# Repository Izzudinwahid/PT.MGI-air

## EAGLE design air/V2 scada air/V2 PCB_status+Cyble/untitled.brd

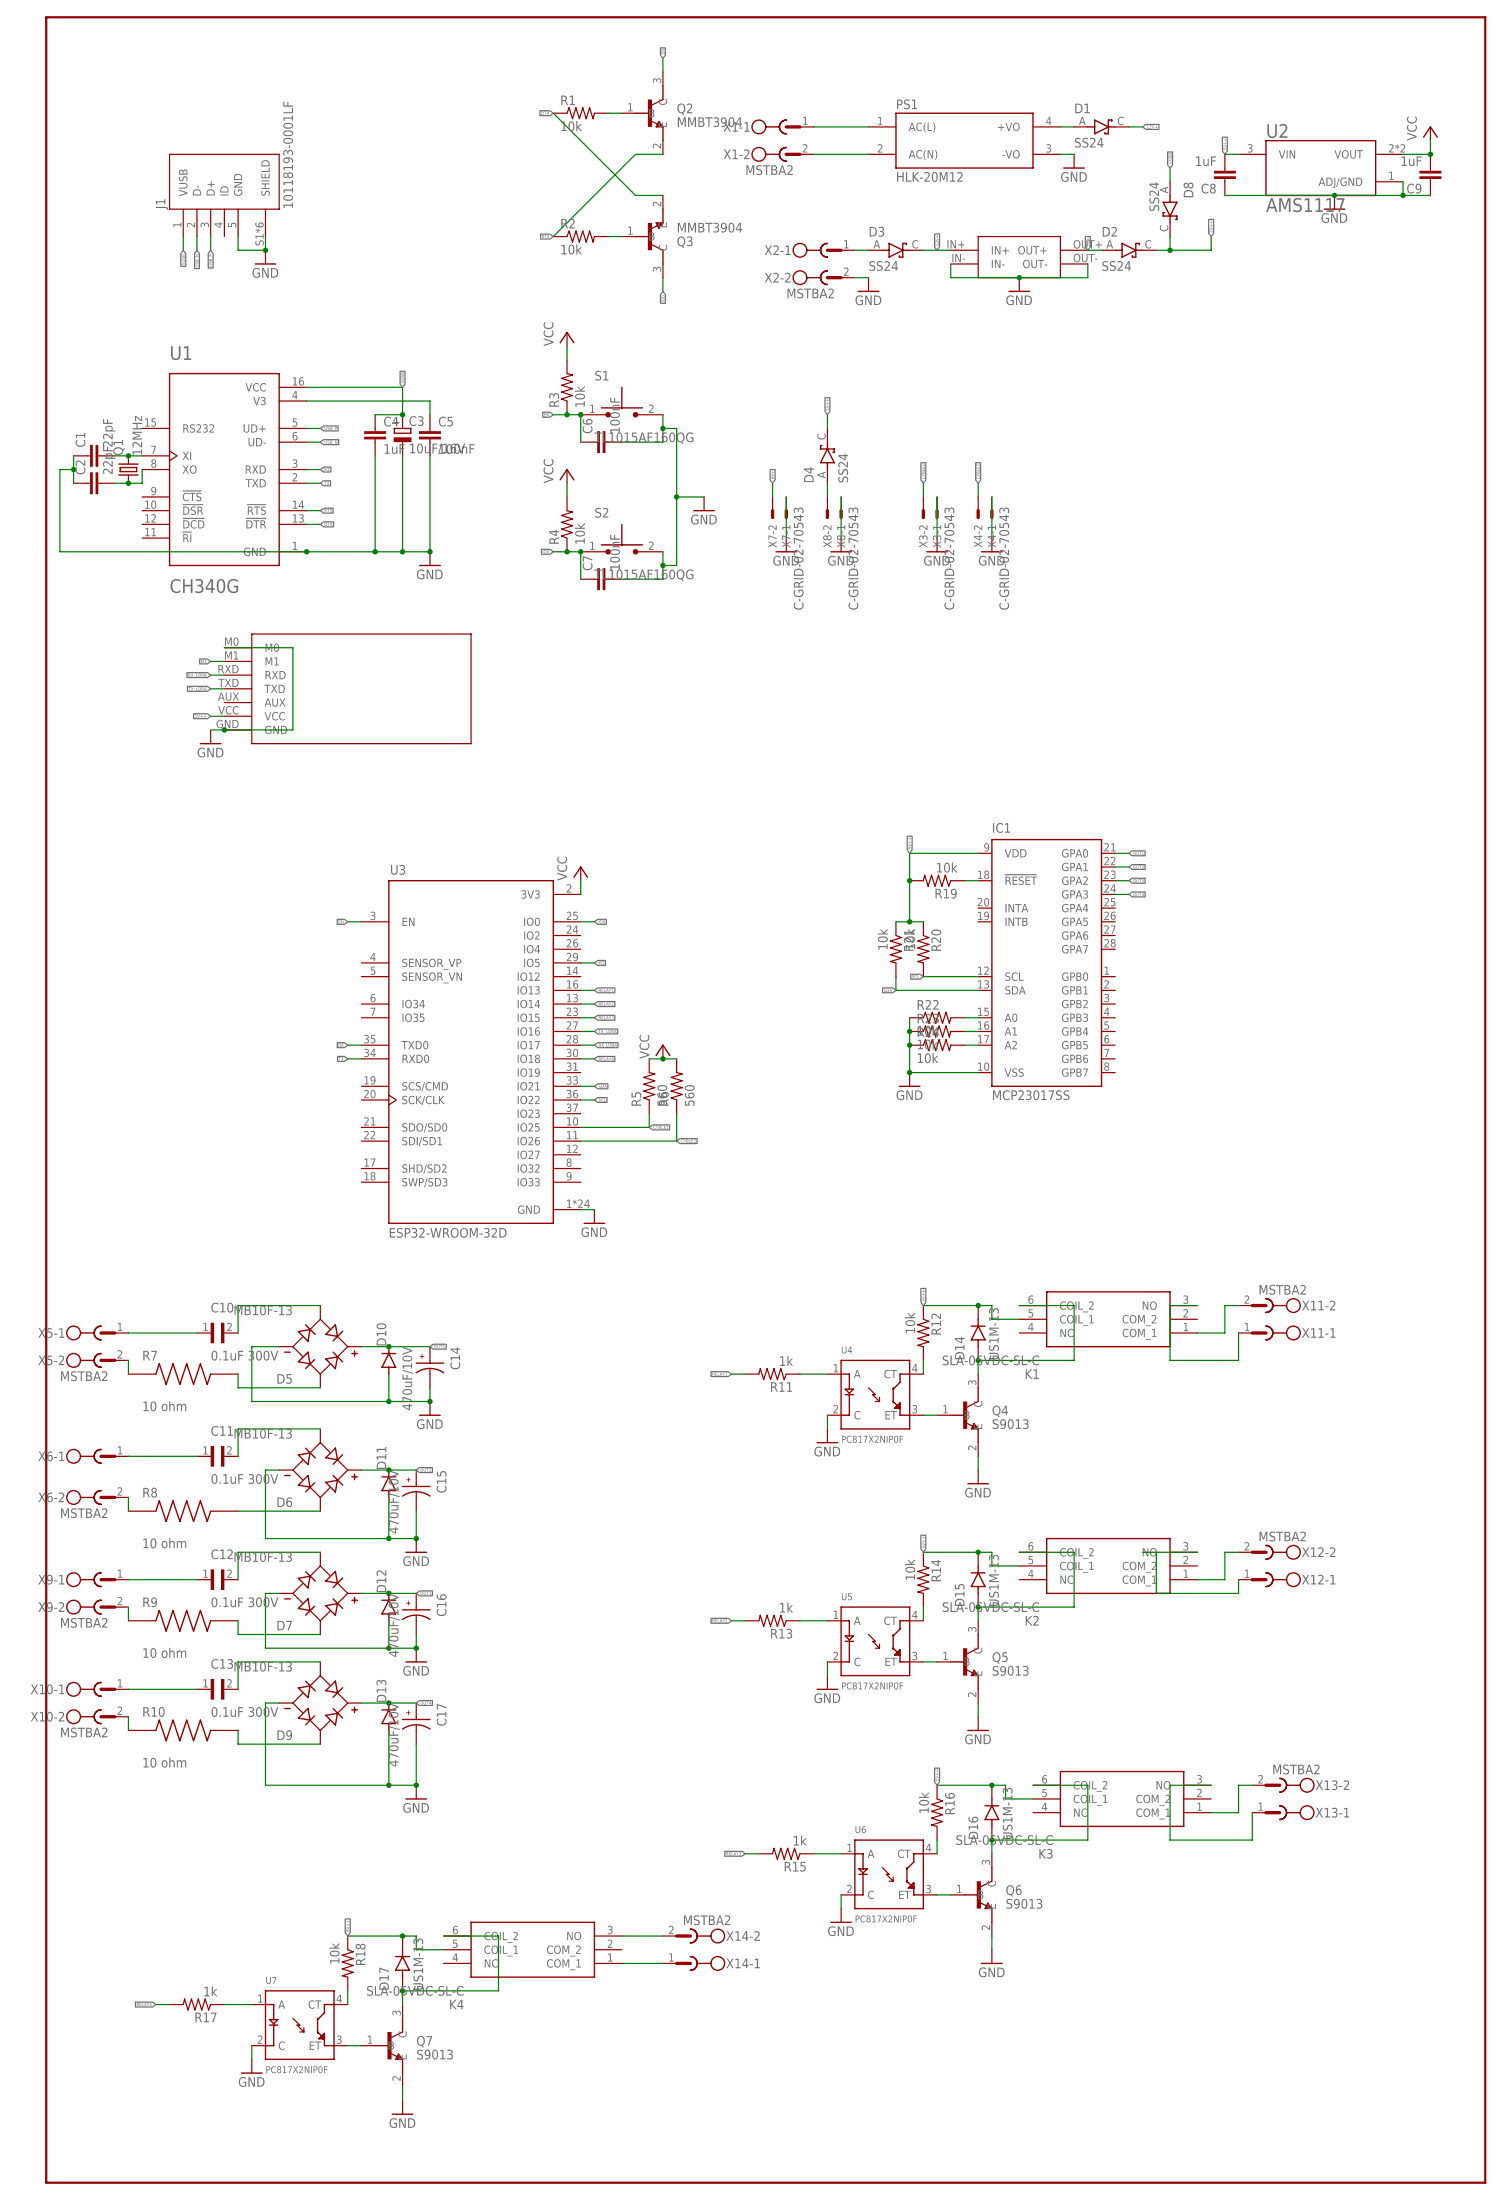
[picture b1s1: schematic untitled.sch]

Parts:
C1, C2: 22pF; C0805K
C3: 10uF/16V; 153CLV-0505
C4, C8, C9: 1uF; C0805K
C5, C6, C7: 100nF; C0805K
C10, C11, C12, C13: 0.1uF 300V; CAPRR1500W60L1750T500H1200
C14, C15, C16, C17: 470uF/10V; CAP_EEEFC1A471AP
D1, D2, D3, D4, D8: SS24; DIOM5336X265N
D5, D6, D7, D9: MB10F-13; DIOB_MB10F-13
D10, D11, D12, D13: DIODE-SOD123; SOD123
D14, D15, D16, D17: US1M-13; DIOM5226X240N
EBYTEE220-900T22D1: EBYTEE220-900T22D
IC1: MCP23017SS; SSOP28
J1: 10118193-0001LF; FCI_10118193-0001LF
K1, K2, K3, K4: SLA-05VDC-SL-C; SLA05VDCSLC
MINI1: MINI560
PS1: HLK-20M12; CONV_HLK-20M12
Q1: 12MHz; SM49
Q2, Q3: MMBT3904; SOT95P240X120-3N
Q4, Q5, Q6, Q7: S9013; SOT95P240X120-3N
R1, R2, R3, R4, R12, R14, R16, R18, R19, R20, R21, R22, R23, R24: 10k; M0805
R5, R6: 560; M0805
R7, R8, R9, R10: 10 ohm; RES_ERJP14J200U
R11, R13, R15, R17: 1k; M0805
S1, S2: TL1015AF160QG; SW_TL1015AF160QG
U1: CH340G; SOIC127P600X180-16N
U2: AMS1117; SOT229P700X180-4N
U3: ESP32-WROOM-32D; MODULE_ESP32-WROOM-32D
U4, U5, U6, U7: PC817X2NIP0F; SOT254P975X400-4N
X1, X2, X5, X6, X9, X10, X11, X12, X13, X14: MSTBA2
X3, X4, X7, X8: C-GRID-02-70543; 70543-02

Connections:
5V+: D2.A, MINI1.OUT+, X7.2
5V++: C8.2, D2.C (K), D4.C (K), D8.C (K), D14.C (K), D15.C (K), D16.C (K), D17.C (K), EBYTEE220-900T22D1.VCC, IC1.9 (VDD), K1.5 (COIL_1), K2.5 (COIL_1), K3.5 (COIL_1), K4.5 (COIL_1), R12.1, R14.1, R16.1, R18.1, R19.2, R20.1, R21.1, U2.3 (VIN)
12V+: D1.C (K), D3.C (K), MINI1.IN+
CYBLE1: R5.1, U3.10 (IO25), X3.2
CYBLE2: R6.1, U3.11 (IO26), X4.2
DTR: Q3.2 (E), R1.1, U1.13 (!DTR)
EN: C6.1, Q2.3 (C), R3.1, S1.1, U3.3 (EN)
GND: C1.1, C2.1, C3.-, C4.2, C5.2, C6.2, C7.2, C8.1, C9.1, C14.2, C15.2, C16.2, C17.2, D5.3 (-), D6.3 (-), D7.3 (-), D9.3 (-), D10.A, D11.A, D12.A, D13.A, EBYTEE220-900T22D1.GND, EBYTEE220-900T22D1.M0, IC1.10 (VSS), J1.5 (GND), J1.S1 (SHIELD), J1.S2 (SHIELD), J1.S3 (SHIELD), J1.S4 (SHIELD), J1.S5 (SHIELD), J1.S6 (SHIELD), MINI1.IN-, MINI1.OUT-, PS1.3 (-VO), Q4.2 (E), Q5.2 (E), Q6.2 (E), Q7.2 (E), R22.1, R23.1, R24.1, S1.2, S2.2, U1.1 (GND), U2.1 (ADJ/GND), U3.1 (GND), U3.15 (GND), U3.38 (GND), U3.39_1 (GND), U3.39_2 (GND), U3.39_3 (GND), U3.39_4 (GND), U3.39_5 (GND), U3.39_6 (GND), U3.39_7 (GND), U3.39_8 (GND), U3.39_9 (GND), U3.39_10 (GND), U3.39_11 (GND), U3.39_12 (GND), U3.39_13 (GND), U3.39_14 (GND), U3.39_15 (GND), U3.39_16 (GND), U3.39_17 (GND), U3.39_18 (GND), U3.39_19 (GND), U3.39_20 (GND), U3.39_21 (GND), U4.2 (C), U5.2 (C), U6.2 (C), U7.2 (C), X2.2, X3.1, X4.1, X7.1, X8.1
IO0: C7.1, Q3.3 (C), R4.1, S2.1, U3.25 (IO0)
M1: EBYTEE220-900T22D1.M1, U3.29 (IO5)
unnamed: PS1.1 (AC(L)), X1.1
unnamed: C5.1, U1.4 (V3)
unnamed: Q2.1 (B), R1.2
unnamed: C1.2, Q1.2, U1.7 (XI)
unnamed: C2.2, Q1.1, U1.8 (XO)
unnamed: Q3.1 (B), R2.2
unnamed: PS1.2 (AC(N)), X1.2
unnamed: C10.1, X5.1
unnamed: D1.A, PS1.4 (+VO)
unnamed: D3.A, X2.1
unnamed: C11.1, X6.1
unnamed: D4.A, X8.2
unnamed: C12.1, X9.1
unnamed: C13.1, X10.1
unnamed: C10.2, D5.4 (AC2)
unnamed: C11.2, D6.4 (AC2)
unnamed: C12.2, D7.4 (AC2)
unnamed: C13.2, D9.4 (AC2)
unnamed: R11.1, U4.1 (A)
unnamed: Q4.1 (B), U4.3 (ET)
unnamed: R12.2, U4.4 (CT)
unnamed: K1.1 (COM_1), X11.2
unnamed: K1.3 (NO), X11.1
unnamed: D14.A, K1.6 (COIL_2), Q4.3 (C)
unnamed: IC1.18 (!RESET), R19.1
unnamed: R13.1, U5.1 (A)
unnamed: R10.1, X10.2
unnamed: R9.1, X9.2
unnamed: R8.1, X6.2
unnamed: R7.1, X5.2
unnamed: D9.2 (AC1), R10.2
unnamed: D7.2 (AC1), R9.2
unnamed: D6.2 (AC1), R8.2
unnamed: D5.2 (AC1), R7.2
unnamed: Q5.1 (B), U5.3 (ET)
unnamed: R14.2, U5.4 (CT)
unnamed: D15.A, K2.6 (COIL_2), Q5.3 (C)
unnamed: K2.1 (COM_1), X12.2
unnamed: K2.3 (NO), X12.1
unnamed: IC1.15 (A0), R22.2
unnamed: R15.1, U6.1 (A)
unnamed: Q6.1 (B), U6.3 (ET)
unnamed: R16.2, U6.4 (CT)
unnamed: D16.A, K3.6 (COIL_2), Q6.3 (C)
unnamed: K3.1 (COM_1), X13.2
unnamed: K3.3 (NO), X13.1
unnamed: IC1.16 (A1), R23.2
unnamed: R17.1, U7.1 (A)
unnamed: Q7.1 (B), U7.3 (ET)
unnamed: R18.2, U7.4 (CT)
unnamed: D17.A, K4.6 (COIL_2), Q7.3 (C)
unnamed: K4.3 (NO), X14.2
unnamed: K4.1 (COM_1), X14.1
unnamed: IC1.17 (A2), R24.2
OUT1: C14.1, D5.1 (+), D10.C, IC1.21 (GPA0)
OUT2: C15.1, D6.1 (+), D11.C, IC1.22 (GPA1)
OUT3: C16.1, D7.1 (+), D12.C, IC1.23 (GPA2)
OUT4: C17.1, D9.1 (+), D13.C, IC1.24 (GPA3)
RELAY1: R11.2, U3.16 (IO13)
RELAY2: R13.2, U3.13 (IO14)
RELAY3: R15.2, U3.23 (IO15)
RELAY4: R17.2, U3.30 (IO18)
RTS: Q2.2 (E), R2.1, U1.14 (!RTS)
RX: U1.3 (RXD), U3.35 (TXD0)
RX_LORA: EBYTEE220-900T22D1.RXD, U3.28 (IO17)
SCL: IC1.12 (SCL), R20.2, U3.36 (IO22)
SDA: IC1.13 (SDA), R21.2, U3.33 (IO21)
TX: U1.2 (TXD), U3.34 (RXD0)
TX_LORA: EBYTEE220-900T22D1.TXD, U3.27 (IO16)
USB_N: J1.2 (D-), U1.6 (UD-)
USB_P: J1.3 (D+), U1.5 (UD+)
VCC: C9.2, R3.2, R4.2, R5.2, R6.2, U2.2 (VOUT), U2.4 (VOUT), U3.2 (3V3)
VUSB: C3.+, C4.1, D8.A, J1.1 (VUSB), U1.16 (VCC)

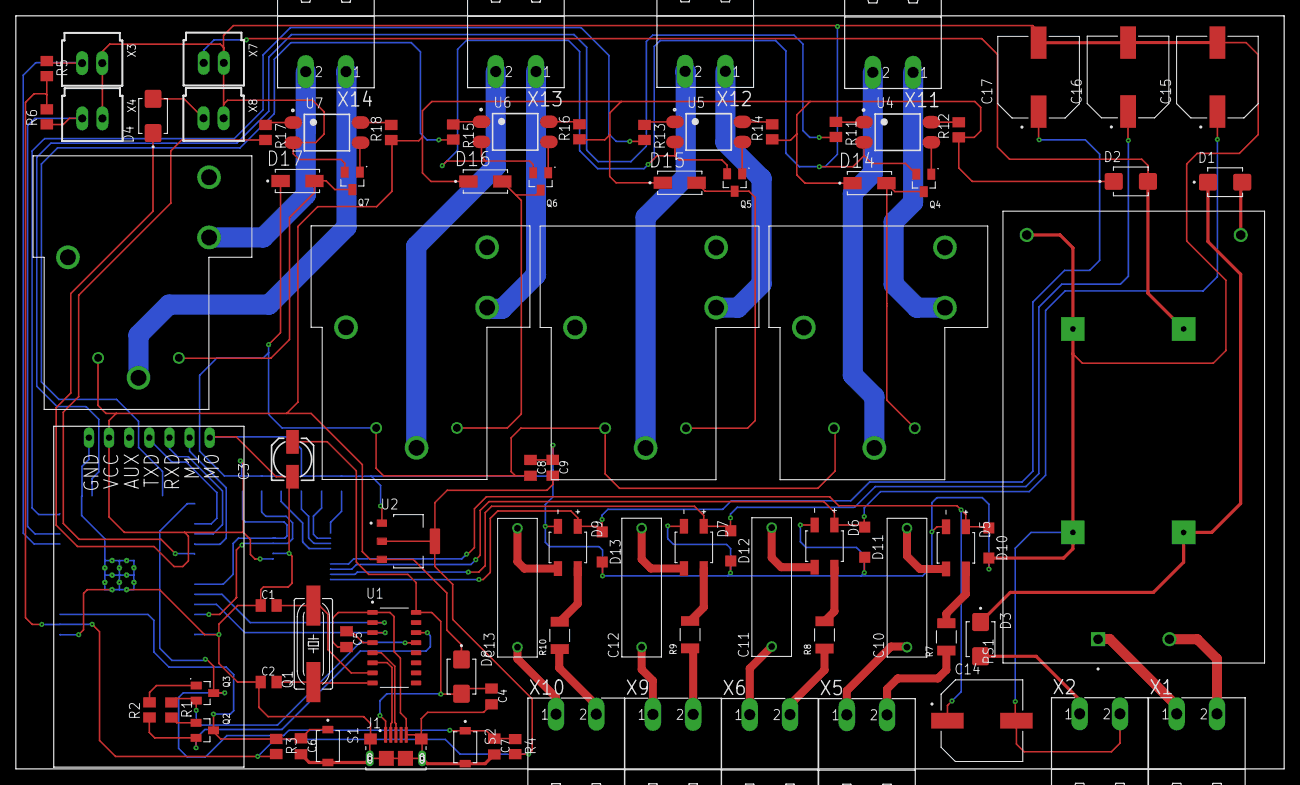
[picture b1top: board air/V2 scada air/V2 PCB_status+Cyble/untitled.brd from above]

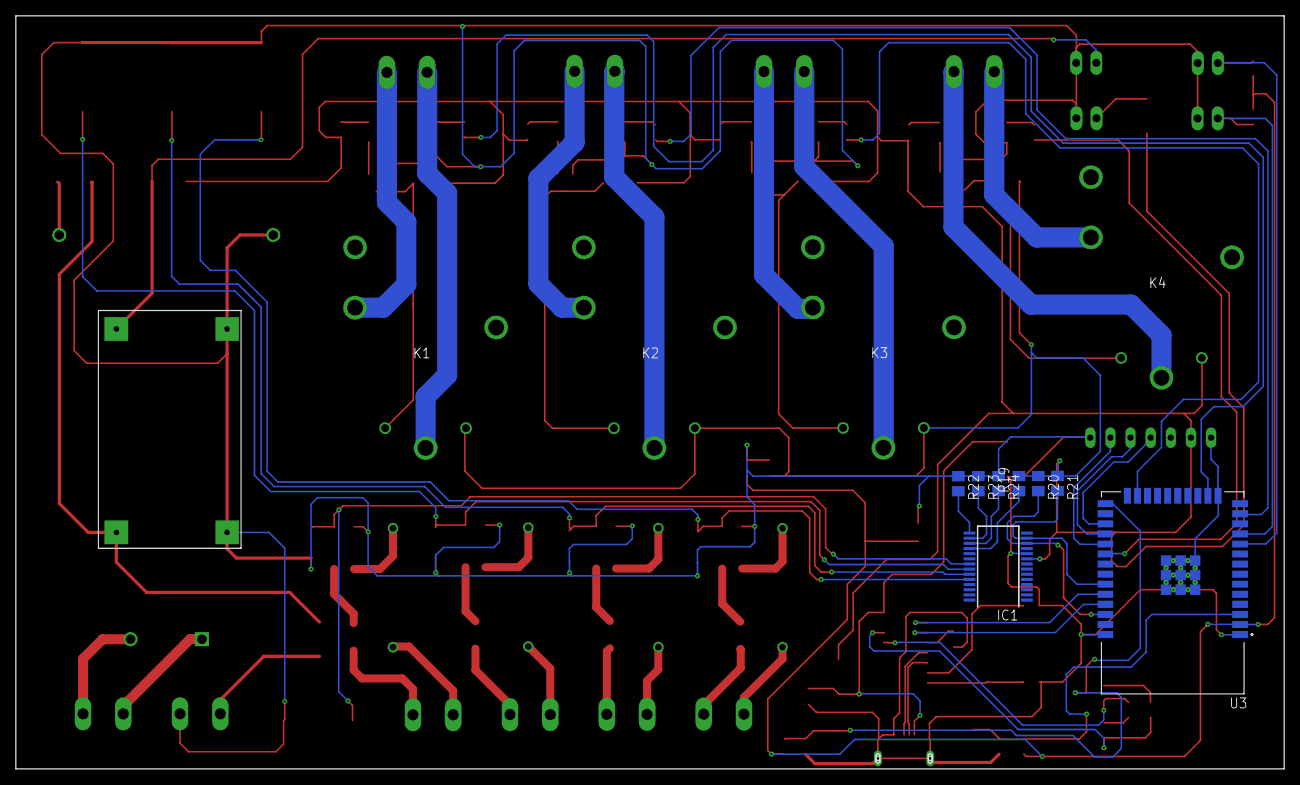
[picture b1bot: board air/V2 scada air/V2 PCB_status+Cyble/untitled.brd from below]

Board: 2 copper layers, 160.0 x 95.0 mm, 97 parts (13 on the bottom side), 83 nets.

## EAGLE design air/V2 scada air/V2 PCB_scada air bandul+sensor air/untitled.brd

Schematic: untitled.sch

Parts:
C1, C2: 22pF; C0805K
C3: 10uF/16V; 153CLV-0505
C4, C8, C9: 1uF; C0805K
C5, C6, C7: 100nF; C0805K
D1, D2, D3, D4, D8: SS24; DIOM5336X265N
D5, D7: US1M-13; DIOM5226X240N
EBYTEE220-900T22D1: EBYTEE220-900T22D
IC1, IC2: MCP23017SS; SSOP28
J1: 10118193-0001LF; FCI_10118193-0001LF
MINI1: MINI560
PS1: HLK-20M12; CONV_HLK-20M12
Q1: 12MHz; SM49
Q2, Q3: MMBT3904; SOT95P240X120-3N
Q5, Q6, Q7, Q8, Q9, Q10, Q11, Q12, Q13, Q14, Q15, Q16, Q17, Q18, Q19, Q20, Q21, Q22, Q23, Q24, Q25, Q26, Q27, Q28: MMBT2222; SOT23-BEC
R1, R2, R3, R4, R7, R8, R59, R60, R61, R62, R63, R64, R65, R66, R67, R68, R69, R70: 10k; M0805
R5, R6: 680; M0805
R11, R13, R15, R17, R19, R21, R23, R25, R27, R29, R31, R33, R35, R37, R39, R41, R43, R45, R47, R49, R51, R53, R55, R57: 1k; M0805
R12, R14, R16, R18, R20, R22, R24, R26, R28, R30, R32, R34, R36, R38, R40, R42, R44, R46, R48, R50, R52, R54, R56, R58: 30k; M0805
S1, S2: TL1015AF160QG; SW_TL1015AF160QG
TTL-RS1: TTL-RS485
U1: CH340G; SOIC127P600X180-16N
U2: AMS1117; SOT229P700X180-4N
U3: ESP32-WROOM-32D; MODULE_ESP32-WROOM-32D
X1, X2, X3: MSTBA2
X4: MSTBA4
X5: C-GRID-04-70543; 70543-04
X7, X8: C-GRID-02-70543; 70543-02
X10, X11, X12, X13, X14, X15, X16, X17, X18, X19, X20, X21, X22, X23, X24, X25, X26, X27, X28, X29, X30, X31, X32, X33: C-GRID-03-70543; 70543-03

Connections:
5V+: D2.A, MINI1.OUT+
5V++: C8.2, D2.C (K), D8.C (K), EBYTEE220-900T22D1.VCC, IC1.9 (VDD), IC2.9 (VDD), R5.2, R6.2, R11.1, R13.1, R15.1, R17.1, R19.1, R21.1, R23.1, R25.1, R27.1, R29.1, R31.1, R33.1, R35.1, R37.1, R39.1, R41.1, R43.1, R45.1, R47.1, R49.1, R51.1, R53.1, R55.1, R57.1, R59.2, R60.2, R61.1, R65.2, R66.2, R67.1, R68.2, TTL-RS1.VCC, U2.3 (VIN), X4.1, X5.4
12V: D1.A, PS1.4 (+VO), X7.2
12V+: D1.C (K), D3.C (K), D4.C (K), MINI1.IN+, R12.1, R14.1, R16.1, R18.1, R20.1, R22.1, R24.1, R26.1, R28.1, R30.1, R32.1, R34.1, R36.1, R38.1, R40.1, R42.1, R44.1, R46.1, R48.1, R50.1, R52.1, R54.1, R56.1, R58.1, X3.1, X10.3, X11.3, X12.3, X13.3, X14.3, X15.3, X16.3, X17.3, X18.3, X19.3, X20.3, X21.3, X22.3, X23.3, X24.3, X25.3, X26.3, X27.3, X28.3, X29.3, X30.3, X31.3, X32.3, X33.3
A+: TTL-RS1.A, X4.2
B-: TTL-RS1.B, X4.3
DTR: Q3.2 (E), R1.1, U1.13 (!DTR)
EN: C6.1, Q2.3 (C), R3.1, S1.1, U3.3 (EN)
GND: C1.1, C2.1, C3.-, C4.2, C5.2, C6.2, C7.2, C8.1, C9.1, EBYTEE220-900T22D1.GND, EBYTEE220-900T22D1.M0, IC1.10 (VSS), IC2.10 (VSS), J1.5 (GND), J1.S1 (SHIELD), J1.S2 (SHIELD), J1.S3 (SHIELD), J1.S4 (SHIELD), J1.S5 (SHIELD), J1.S6 (SHIELD), MINI1.IN-, MINI1.OUT-, PS1.3 (-VO), R62.2, R63.2, R64.2, R69.2, R70.2, S1.2, S2.2, TTL-RS1.GND, U1.1 (GND), U2.1 (ADJ/GND), U3.1 (GND), U3.15 (GND), U3.38 (GND), U3.39_1 (GND), U3.39_2 (GND), U3.39_3 (GND), U3.39_4 (GND), U3.39_5 (GND), U3.39_6 (GND), U3.39_7 (GND), U3.39_8 (GND), U3.39_9 (GND), U3.39_10 (GND), U3.39_11 (GND), U3.39_12 (GND), U3.39_13 (GND), U3.39_14 (GND), U3.39_15 (GND), U3.39_16 (GND), U3.39_17 (GND), U3.39_18 (GND), U3.39_19 (GND), U3.39_20 (GND), U3.39_21 (GND), X2.2, X3.2, X4.4, X5.1, X7.1, X8.1, X10.1, X11.1, X12.1, X13.1, X14.1, X15.1, X16.1, X17.1, X18.1, X19.1, X20.1, X21.1, X22.1, X23.1, X24.1, X25.1, X26.1, X27.1, X28.1, X29.1, X30.1, X31.1, X32.1, X33.1
IO0: C7.1, Q3.3 (C), R4.1, S2.1, U3.25 (IO0)
M1: EBYTEE220-900T22D1.M1, U3.29 (IO5)
unnamed: D5.C (K), U3.28 (IO17)
unnamed: C5.1, U1.4 (V3)
unnamed: Q2.1 (B), R1.2
unnamed: C1.2, Q1.2, U1.7 (XI)
unnamed: C2.2, Q1.1, U1.8 (XO)
unnamed: Q3.1 (B), R2.2
unnamed: PS1.1 (AC(L)), X1.1
unnamed: PS1.2 (AC(N)), X1.2
unnamed: D3.A, X2.1
unnamed: D4.A, X8.2
unnamed: Q5.B, R12.2
unnamed: IC2.18 (!RESET), R65.1
unnamed: Q5.E, X10.2
unnamed: D7.C (K), EBYTEE220-900T22D1.TXD
unnamed: Q6.B, R14.2
unnamed: IC1.18 (!RESET), R59.1
unnamed: Q6.E, X11.2
unnamed: Q7.B, R16.2
unnamed: IC1.15 (A0), R62.1
unnamed: Q7.E, X12.2
unnamed: Q8.B, R18.2
unnamed: IC1.16 (A1), R63.1
unnamed: Q8.E, X13.2
unnamed: Q9.B, R20.2
unnamed: IC1.17 (A2), R64.1
unnamed: Q9.E, X14.2
unnamed: Q10.B, R22.2
unnamed: IC2.15 (A0), R68.1
unnamed: Q10.E, X15.2
unnamed: Q11.B, R24.2
unnamed: IC2.16 (A1), R69.1
unnamed: Q11.E, X16.2
unnamed: Q12.B, R26.2
unnamed: IC2.17 (A2), R70.1
unnamed: Q12.E, X17.2
unnamed: Q13.B, R28.2
unnamed: Q13.E, X18.2
unnamed: Q14.B, R30.2
unnamed: Q14.E, X19.2
unnamed: Q15.B, R32.2
unnamed: Q15.E, X20.2
unnamed: Q16.B, R34.2
unnamed: Q16.E, X21.2
unnamed: Q17.B, R36.2
unnamed: Q17.E, X22.2
unnamed: Q18.B, R38.2
unnamed: Q18.E, X23.2
unnamed: Q19.B, R40.2
unnamed: Q19.E, X24.2
unnamed: Q20.B, R42.2
unnamed: Q20.E, X25.2
unnamed: Q21.B, R44.2
unnamed: Q21.E, X26.2
unnamed: Q22.B, R46.2
unnamed: Q22.E, X27.2
unnamed: Q23.B, R48.2
unnamed: Q23.E, X28.2
unnamed: Q24.B, R50.2
unnamed: Q24.E, X29.2
unnamed: Q25.B, R52.2
unnamed: Q25.E, X30.2
unnamed: Q26.B, R54.2
unnamed: Q26.E, X31.2
unnamed: Q27.B, R56.2
unnamed: Q27.E, X32.2
unnamed: Q28.B, R58.2
unnamed: Q28.E, X33.2
O1: IC1.21 (GPA0), Q5.C, R11.2
O2: IC1.22 (GPA1), Q6.C, R13.2
O3: IC1.23 (GPA2), Q7.C, R15.2
O4: IC1.24 (GPA3), Q8.C, R17.2
O5: IC1.25 (GPA4), Q9.C, R19.2
O6: IC1.26 (GPA5), Q10.C, R21.2
O7: IC1.27 (GPA6), Q11.C, R23.2
O8: IC1.28 (GPA7), Q12.C, R25.2
O9: IC1.1 (GPB0), Q13.C, R27.2
O10: IC1.2 (GPB1), Q14.C, R29.2
O11: IC1.3 (GPB2), Q15.C, R31.2
O12: IC1.4 (GPB3), Q16.C, R33.2
O13: IC1.5 (GPB4), Q17.C, R35.2
O14: IC1.6 (GPB5), Q18.C, R37.2
O15: IC1.7 (GPB6), Q19.C, R39.2
O16: IC1.8 (GPB7), Q20.C, R41.2
O17: IC2.21 (GPA0), Q21.C, R43.2
O18: IC2.22 (GPA1), Q22.C, R45.2
O19: IC2.23 (GPA2), Q23.C, R47.2
O20: IC2.24 (GPA3), Q24.C, R49.2
O21: IC2.25 (GPA4), Q25.C, R51.2
O22: IC2.26 (GPA5), Q26.C, R53.2
O23: IC2.27 (GPA6), Q27.C, R55.2
O24: IC2.28 (GPA7), Q28.C, R57.2
ROTATY-CCW: R6.1, U3.23 (IO15), X5.2
ROTATY-CW: R5.1, U3.13 (IO14), X5.3
RTS: Q2.2 (E), R2.1, U1.14 (!RTS)
RX: U1.3 (RXD), U3.35 (TXD0)
RX_LORA: D5.A, EBYTEE220-900T22D1.RXD, R7.1
RX_RS485: TTL-RS1.RX, U3.31 (IO19)
SCL: IC1.12 (SCL), IC2.12 (SCL), R60.1, R66.1, U3.36 (IO22)
SDA: IC1.13 (SDA), IC2.13 (SDA), R61.2, R67.2, U3.33 (IO21)
TX: U1.2 (TXD), U3.34 (RXD0)
TX_LORA: D7.A, R8.1, U3.27 (IO16)
TX_RS485: TTL-RS1.TX, U3.30 (IO18)
USB_N: J1.2 (D-), U1.6 (UD-)
USB_P: J1.3 (D+), U1.5 (UD+)
VCC: C9.2, R3.2, R4.2, R7.2, R8.2, U2.2 (VOUT), U2.4 (VOUT), U3.2 (3V3)
VUSB: C3.+, C4.1, D8.A, J1.1 (VUSB), U1.16 (VCC)

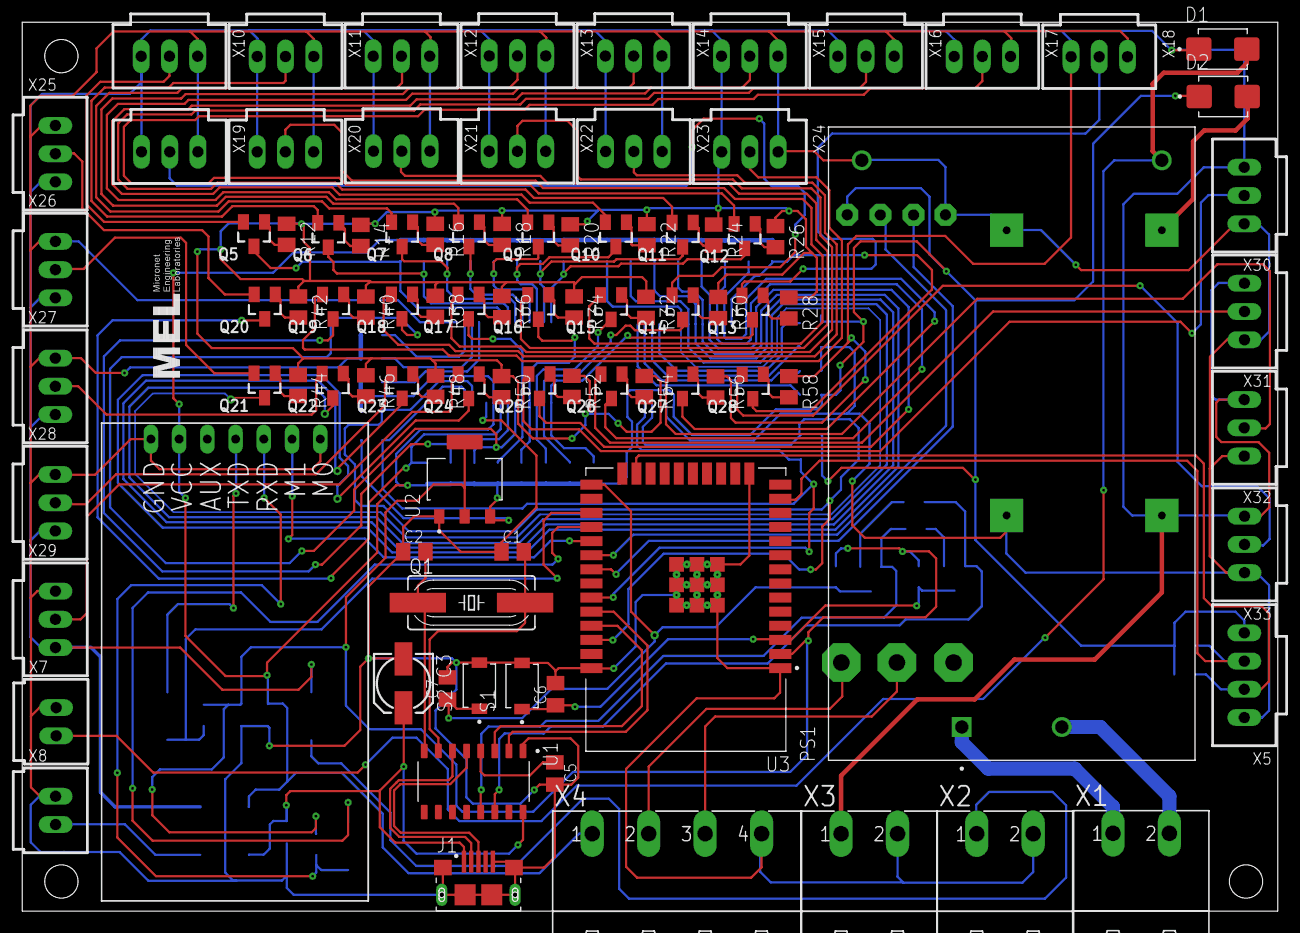
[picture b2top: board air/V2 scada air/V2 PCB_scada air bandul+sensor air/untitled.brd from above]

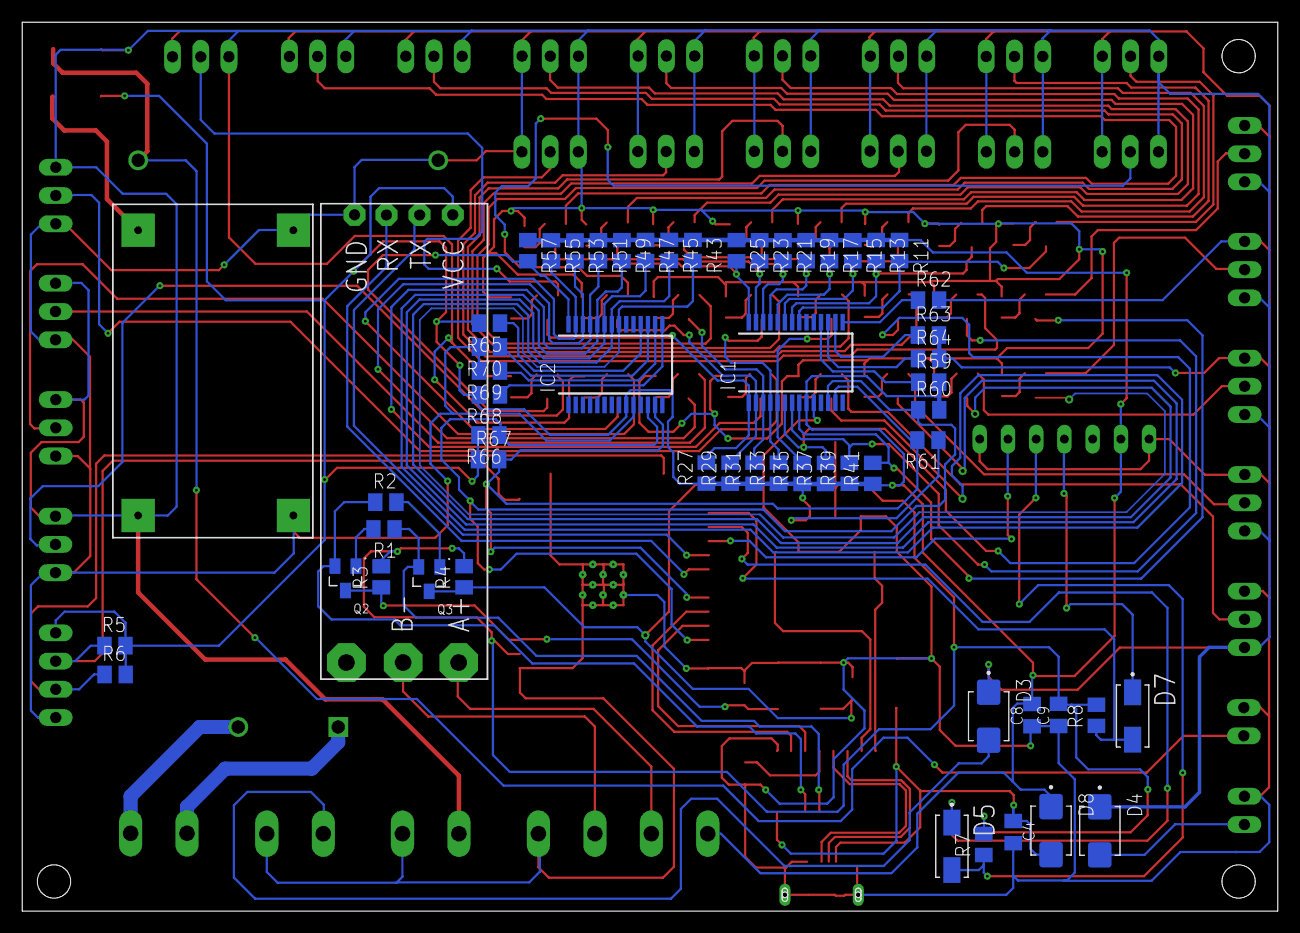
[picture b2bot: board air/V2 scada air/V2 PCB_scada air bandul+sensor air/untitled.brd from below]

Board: 2 copper layers, 113.0 x 80.0 mm, 154 parts (58 on the bottom side), 117 nets.
